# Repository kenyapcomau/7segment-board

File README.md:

# 7 segment 2 digit board

These are the design files for a 7 segment board similar to [6 segment 2 digit board](https://hackaday.io/project/175397-6-segment-2-digit-led-board). Up to 3 boards can be cascaded for 6 digits.

This is a multiplexed design with 7 cathode segment drive lines plus 1 colon line, and up to 6 anode digit drive lines. The cathode drive lines are taken high to turn on the transistors, while the anode drive lines are taken low to turn on the transistors.

## Versioning

Release October 2020

## Notes

Most components are installed on the back side and the LEDs are installed on the front side.

The NPN transistors need a gain > 20 and the PNP transistors need a gain > 40. A bit more margin is recommended.

Note the the LED supply voltage will need to be higher than 4x the LED drop and the cathode current limiting resistor should be calculated accordingly. So 5V will not be sufficient and also a buffer stage will be needed for most MCUs. For example with a 12V supply and green (not emerald) LEDs, the voltage drop per LED is 2V. The transistor drops will be around 0.8V. That leaves 2.2V to be dropped across the resistor. A 220Ω resistor gives 10mA through the LED. For 4 digits multiplexed this is effectively 2.5mA. Modern LEDs are efficient enough to shine brightly at such currents. For dimming, use PWM.

When cascading only one board needs to be fully populated. The (up to 2) others only need the LEDs, the anode driver transistors, and its resistors. Also the PNP transistor base drive resistor leads are extended to fit the anode drive line connector holes for the digit select, starting with pin 1 for the leftmost digit.

The schematic shows cathode current limiting resistors in parallel with TM1810 constant current ICs. Only one needs to be installed. Only TM1810-30 was available to me and 30mA is too high a current for 3mm LEDs, even multiplexed so I stuck with the resistors.

## Authors

* **Ken Yap**

## License

See the [LICENSE](LICENSE.md) file for license rights and limitations (MIT).

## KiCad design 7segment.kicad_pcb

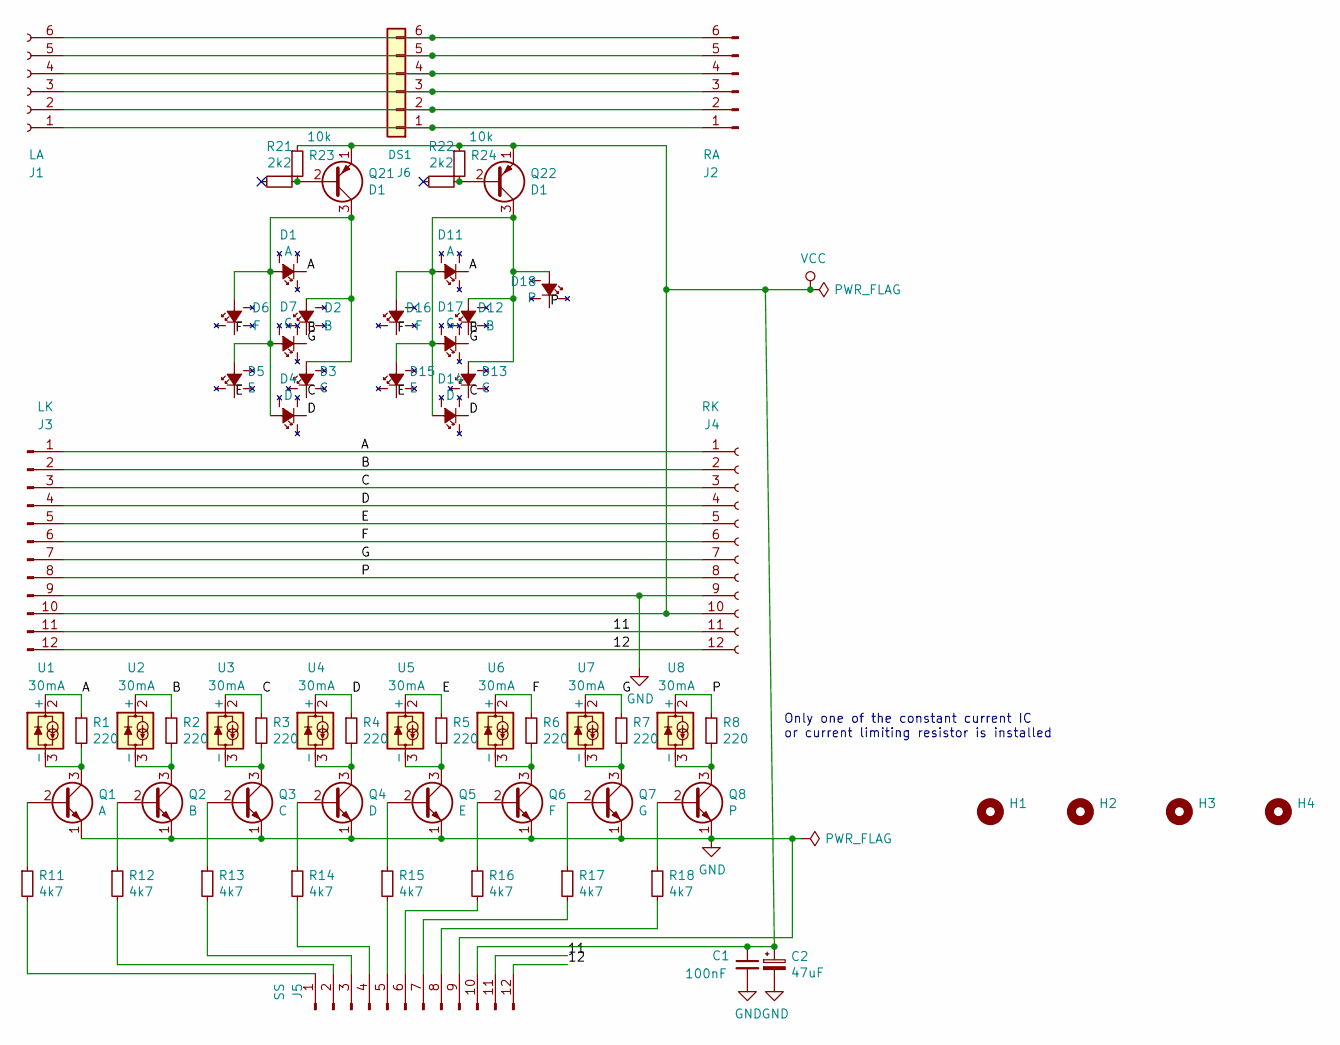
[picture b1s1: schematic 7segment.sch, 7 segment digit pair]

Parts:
C1: 100nF; C_Rect_L7.0mm_W2.0mm_P5.00mm
C2: 47uF; CP_Radial_D5.0mm_P2.50mm
D1, D11: A; LED_D3.0mmx4
D2, D12: B; LED_D3.0mmx4
D3, D13: C; LED_D3.0mmx4
D4, D14: D; LED_D3.0mmx4
D5, D15: E; LED_D3.0mmx4
D6, D16: F; LED_D3.0mmx4
D7, D17: G; LED_D3.0mmx4
D18: P; LED_D3.0mm-colon
H1, H2, H3, H4: MountingHole; MountingHole_3.5mm
J1: LA; PinSocket_1x06_P2.54mm_Horizontal
J2: RA; PinHeader_1x06_P2.54mm_Horizontal
J3: LK; PinHeader_1x12_P2.54mm_Horizontal
J4: RK; PinSocket_1x12_P2.54mm_Horizontal
J5: SS; PinHeader_1x12_P2.54mm_Vertical
J6: DS1; 2X3
Q1: A; TO-92
Q2: B; TO-92
Q3: C; TO-92
Q4: D; TO-92
Q5: E; TO-92
Q6: F; TO-92
Q7: G; TO-92
Q8: P; TO-92
Q21, Q22: D1; TO-92
R1, R2, R3, R4, R5, R6, R7, R8: 220; R_Axial_DIN0309_L9.0mm_D3.2mm_P12.70mm_Horizontal
R11, R12, R13, R14, R15, R16, R17, R18: 4k7; R_Axial_DIN0309_L9.0mm_D3.2mm_P12.70mm_Horizontal
R21, R22: 2k2; R_Axial_DIN0309_L9.0mm_D3.2mm_P12.70mm_Horizontal
R23, R24: 10k; R_Axial_DIN0309_L9.0mm_D3.2mm_P12.70mm_Horizontal
U1, U2, U3, U4, U5, U6, U7, U8: 30mA; SOT-23

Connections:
/11: J3.11, J4.11, J5.11
/12: J3.12, J4.12, J5.12
/A: D1.1 (K), D11.1 (K), J3.1, J4.1, R1.1, U1.2 (+)
/B: D2.1 (K), D12.1 (K), J3.2, J4.2, R2.1, U2.2 (+)
/C: D3.1 (K), D13.1 (K), J3.3, J4.3, R3.1, U3.2 (+)
/D: D4.1 (K), D14.1 (K), J3.4, J4.4, R4.1, U4.2 (+)
/E: D5.1 (K), D15.1 (K), J3.5, J4.5, R5.1, U5.2 (+)
/F: D6.1 (K), D16.1 (K), J3.6, J4.6, R6.1, U6.2 (+)
/G: D7.1 (K), D17.1 (K), J3.7, J4.7, R7.1, U7.2 (+)
/P: D18.1 (K), J3.8, J4.8, R8.1, U8.2 (+)
GND: C1.2, C2.2, J3.9, J4.9, J5.9, Q1.1 (E), Q2.1 (E), Q3.1 (E), Q4.1 (E), Q5.1 (E), Q6.1 (E), Q7.1 (E), Q8.1 (E)
unnamed: D1.2 (A), D2.2 (A), D3.2 (A), D4.2 (A), D5.2 (A), D6.2 (A), D7.2 (A), Q21.3 (C)
unnamed: D11.2 (A), D12.2 (A), D13.2 (A), D14.2 (A), D15.2 (A), D16.2 (A), D17.2 (A), D18.2 (A), Q22.3 (C)
unnamed: J1.1, J2.1, J6.1
unnamed: J1.2, J2.2, J6.2
unnamed: J1.3, J2.3, J6.3
unnamed: J1.4, J2.4, J6.4
unnamed: J1.5, J2.5, J6.5
unnamed: J1.6, J2.6, J6.6
unnamed: J5.1, R11.2
unnamed: J5.2, R12.2
unnamed: J5.3, R13.2
unnamed: J5.4, R14.2
unnamed: J5.5, R15.2
unnamed: J5.6, R16.2
unnamed: J5.7, R17.2
unnamed: J5.8, R18.2
unnamed: Q1.2 (B), R11.1
unnamed: Q1.3 (C), R1.2, U1.3 (-)
unnamed: Q2.2 (B), R12.1
unnamed: Q2.3 (C), R2.2, U2.3 (-)
unnamed: Q3.2 (B), R13.1
unnamed: Q3.3 (C), R3.2, U3.3 (-)
unnamed: Q4.2 (B), R14.1
unnamed: Q4.3 (C), R4.2, U4.3 (-)
unnamed: Q5.2 (B), R15.1
unnamed: Q5.3 (C), R5.2, U5.3 (-)
unnamed: Q6.2 (B), R16.1
unnamed: Q6.3 (C), R6.2, U6.3 (-)
unnamed: Q7.2 (B), R17.1
unnamed: Q7.3 (C), R7.2, U7.3 (-)
unnamed: Q8.2 (B), R18.1
unnamed: Q8.3 (C), R8.2, U8.3 (-)
unnamed: Q21.2 (B), R21.1, R23.2
unnamed: Q22.2 (B), R22.1, R24.2
VCC: C1.1, C2.1, J3.10, J4.10, J5.10, Q21.1 (E), Q22.1 (E), R23.1, R24.1

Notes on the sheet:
Only one of the constant current IC or current limiting resistor is installed

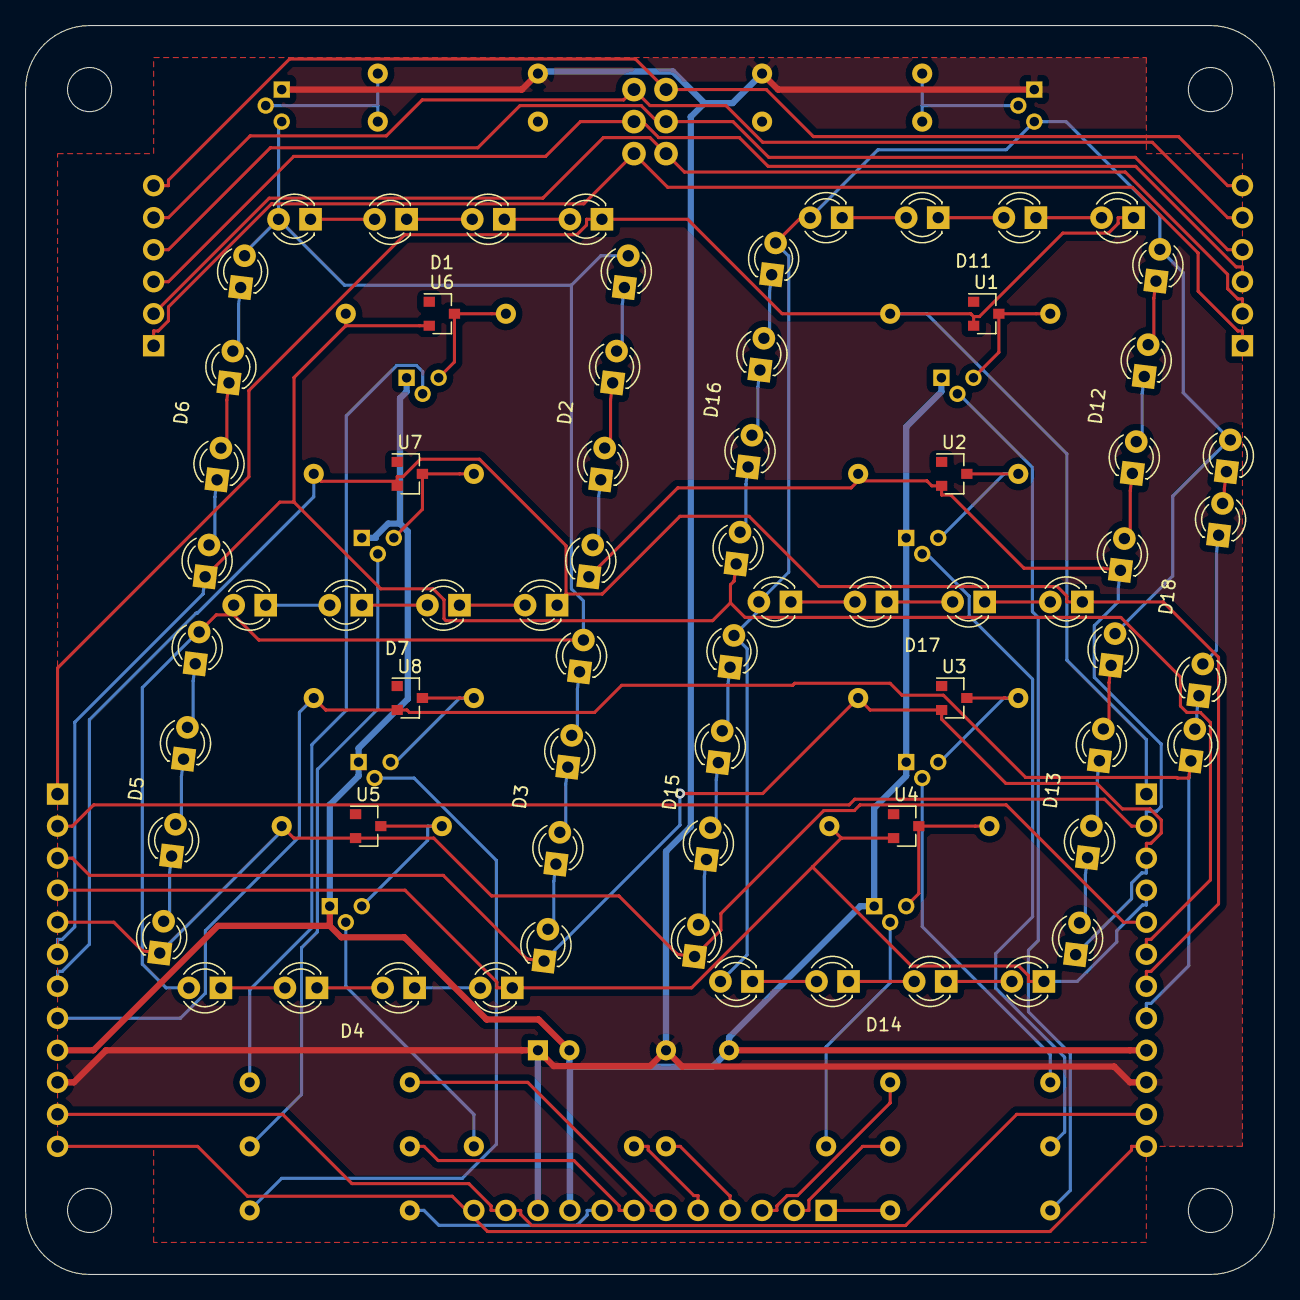
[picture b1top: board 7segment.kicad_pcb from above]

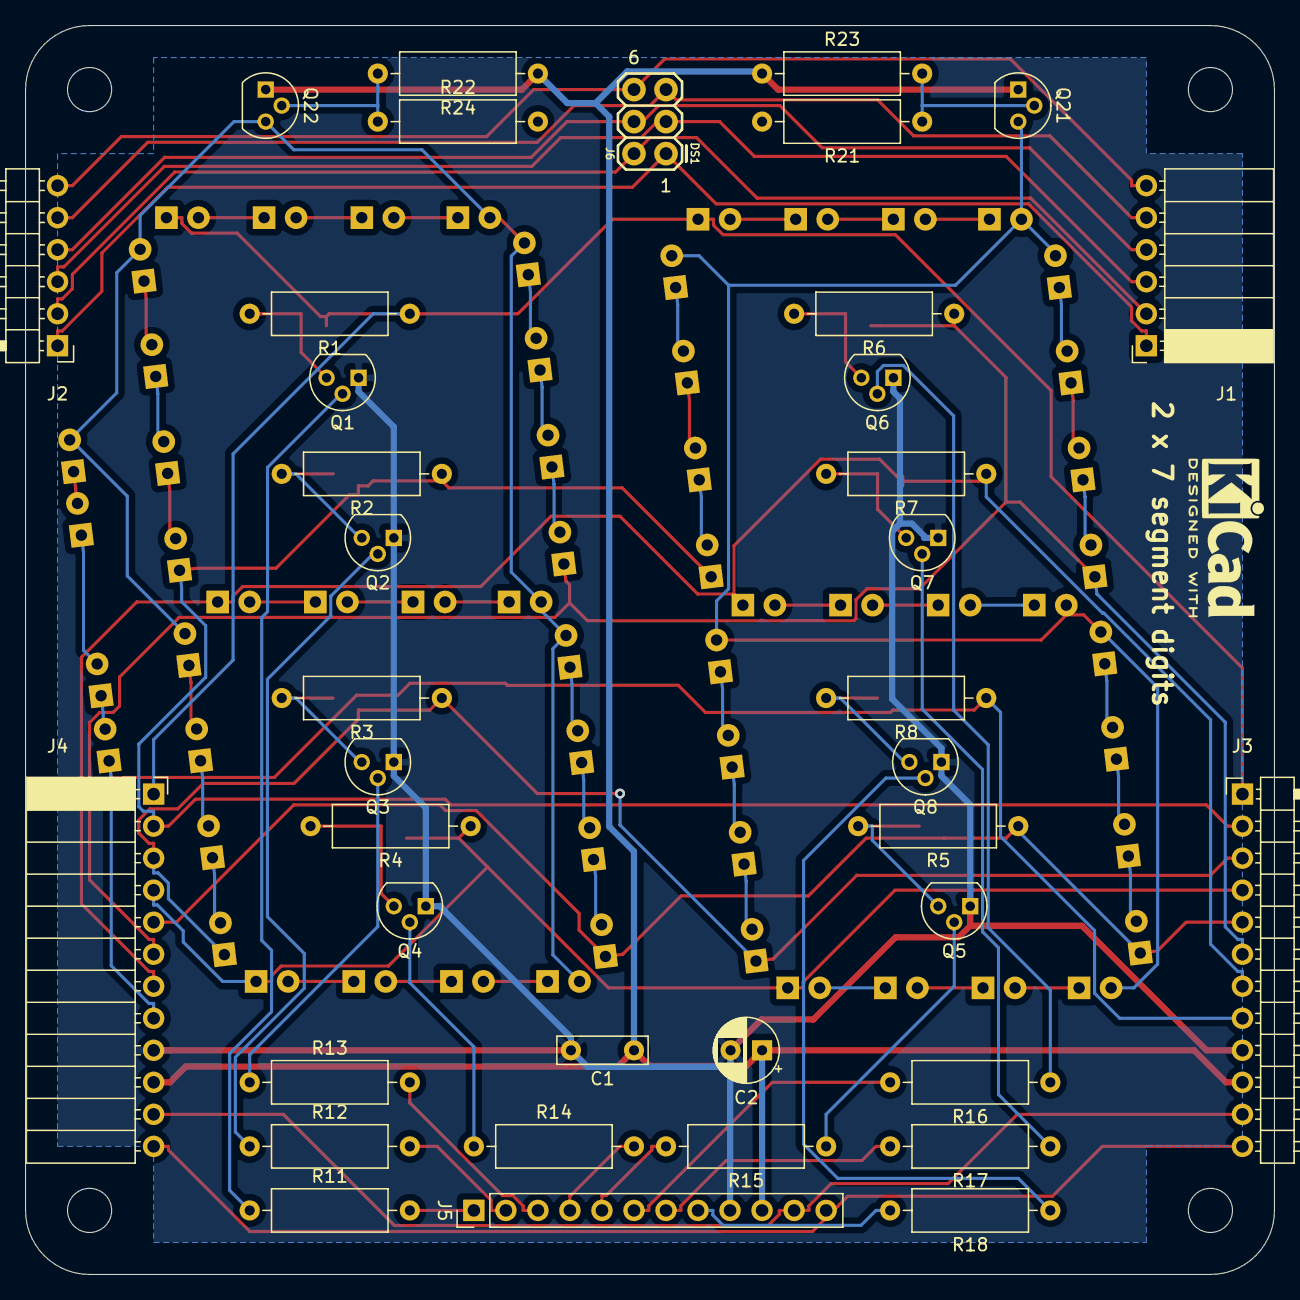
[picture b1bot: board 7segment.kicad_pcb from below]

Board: 2 copper layers, 99.1 x 99.1 mm, 65 parts (38 on the bottom side), 46 nets.

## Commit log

2020-10-16 Initial release
